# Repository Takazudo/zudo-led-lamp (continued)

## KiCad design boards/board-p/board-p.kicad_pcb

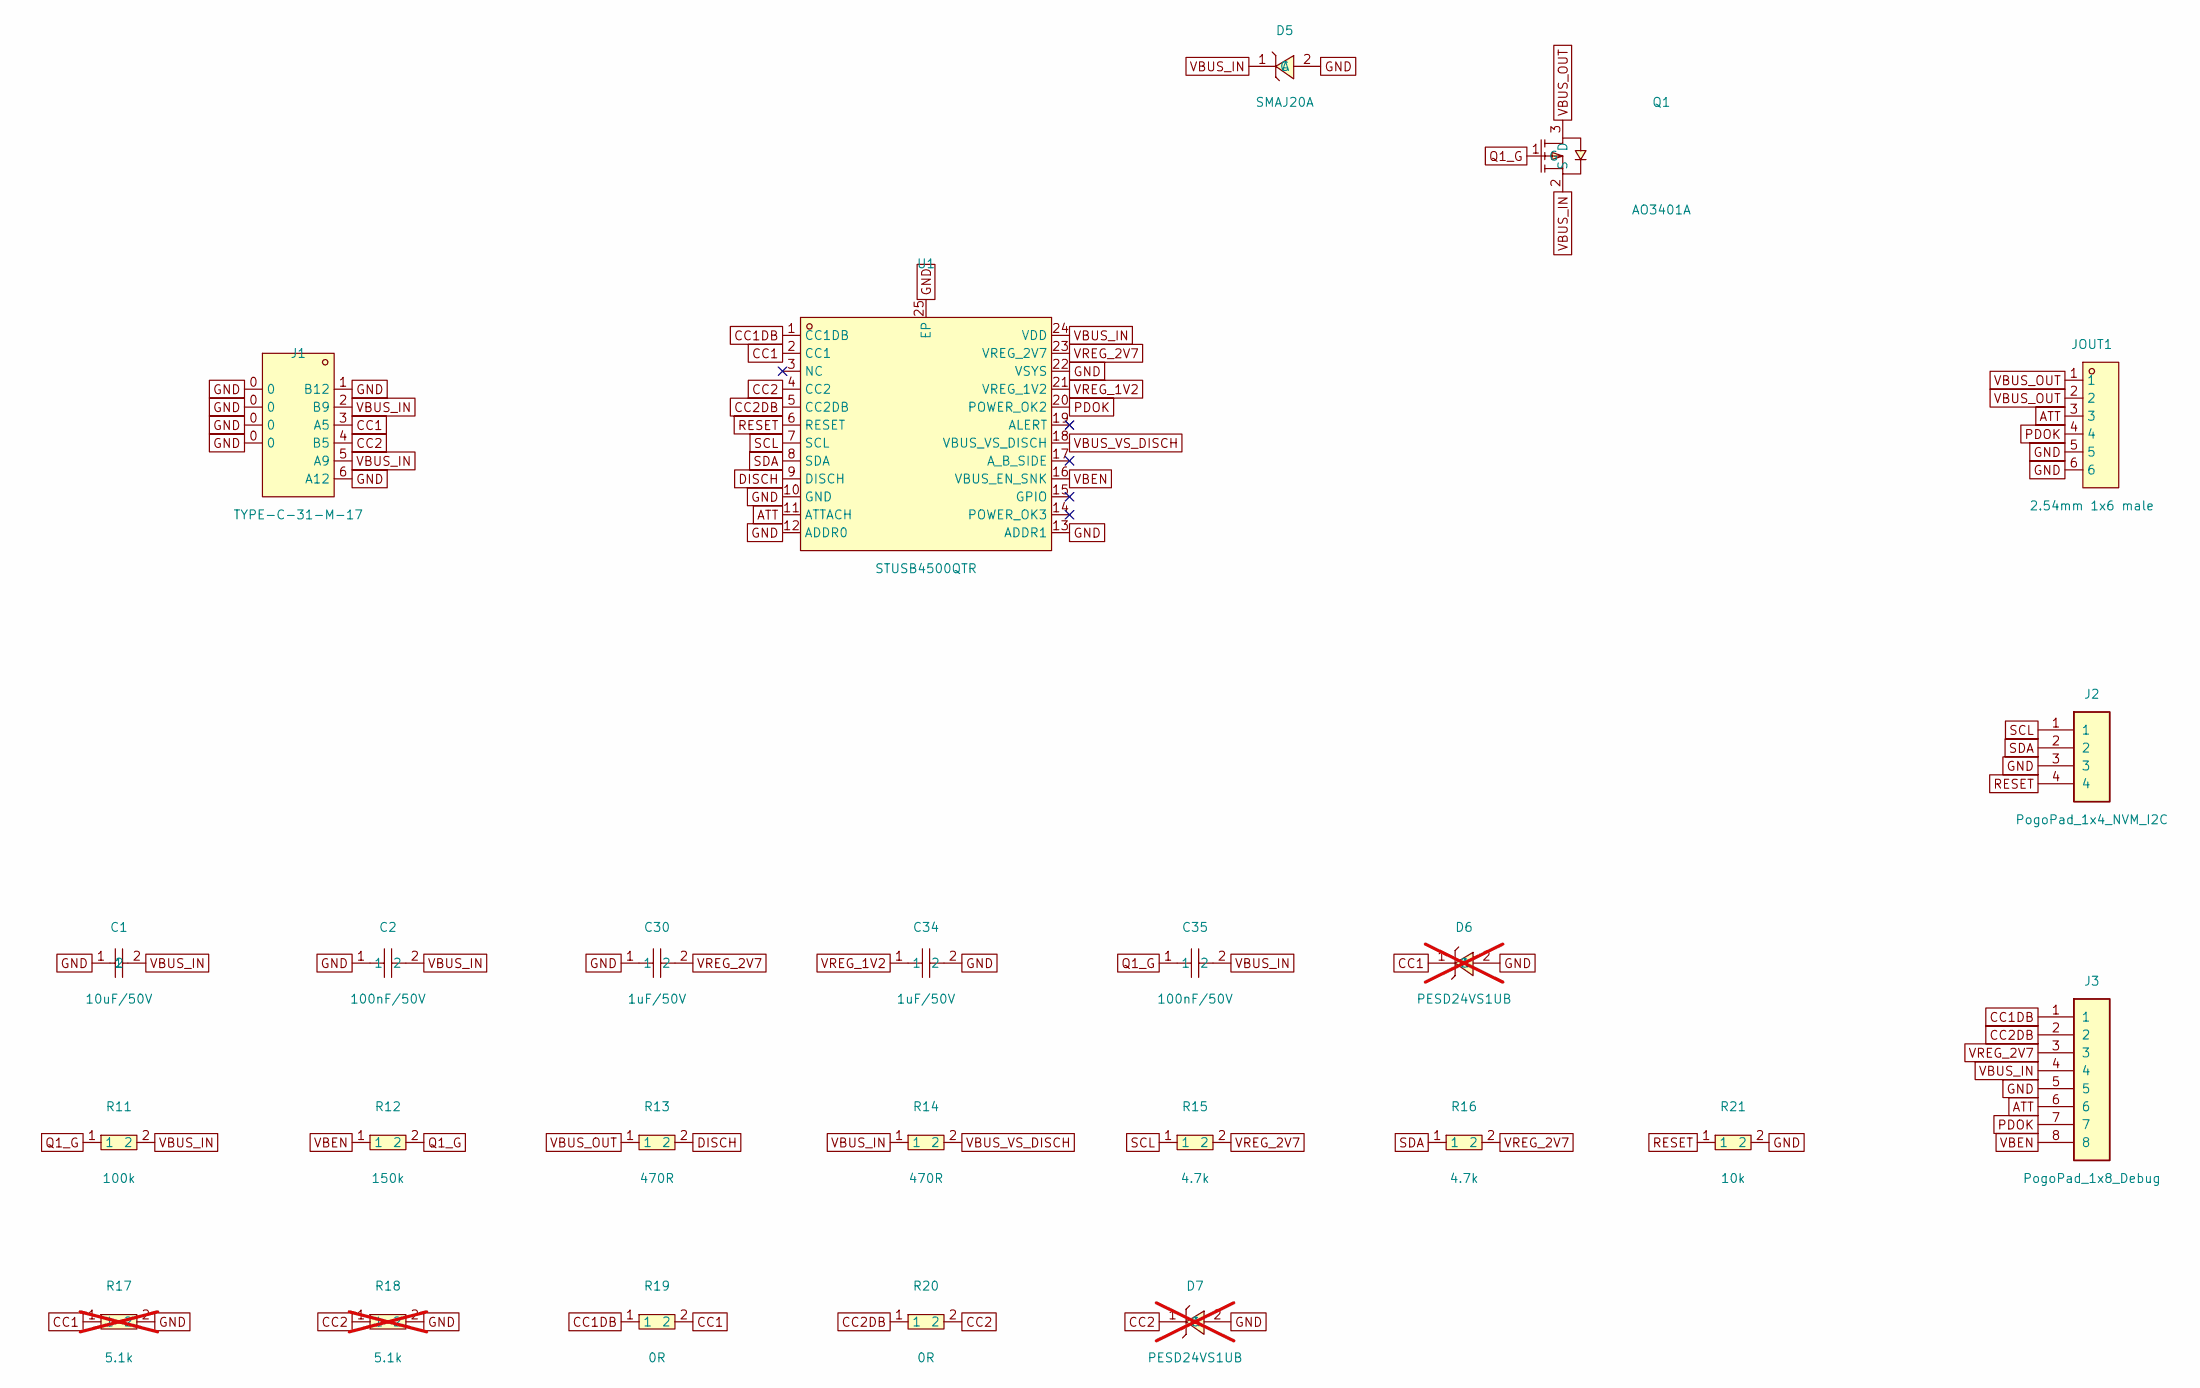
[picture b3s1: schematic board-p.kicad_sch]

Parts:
C1: 10uF/50V; C1206; LCSC C13585
C2, C35: 100nF/50V; C0603; LCSC C14663
C30, C34: 1uF/50V; C0603; LCSC C15849
D5: SMAJ20A; SMA_L4.2-W2.6-LS5.3-RD; LCSC C571370
D6, D7: PESD24VS1UB; SOD-523_L1.2-W0.8-LS1.6-RD; LCSC C85382; not fitted
J1: TYPE-C-31-M-17; USB-C-SMD_10P-P1.00-L6.8-W8.9; LCSC C283540
J2: PogoPad_1x4_NVM_I2C; PogoPad_1x04_P2.54mm
J3: PogoPad_1x8_Debug; PogoPad_1x08_P2.54mm
JOUT1: 2.54mm 1x6 male; HDR-TH_6P-P2.54-V-M; LCSC C492405
Q1: AO3401A; SOT-23_L2.9-W1.3-P1.90-LS2.4-BR; LCSC C347476
R11: 100k; R0603; LCSC C25803
R12: 150k; R0603; LCSC C22807
R13, R14: 470R; R0603; LCSC C23179
R15, R16: 4.7k; R0603; LCSC C23162
R17, R18: 5.1k; R0603; LCSC C23186; not fitted
R19, R20: 0R; R0603; LCSC C21189
R21: 10k; R0805; LCSC C17414
U1: STUSB4500QTR; QFN-24_L4.0-W4.0-P0.50-BL-EP2.8; LCSC C2678061

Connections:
ATT: J3.6, JOUT1.3, U1.11 (ATTACH)
CC1: D6.1 (C), J1.3 (A5), R17.1, R19.2, U1.2 (CC1)
CC1DB: J3.1, R19.1, U1.1 (CC1DB)
CC2: D7.1 (C), J1.4 (B5), R18.1, R20.2, U1.4 (CC2)
CC2DB: J3.2, R20.1, U1.5 (CC2DB)
DISCH: R13.2, U1.9 (DISCH)
GND: C1.1, C2.1, C30.1, C34.2, D5.2 (A), D6.2 (A), D7.2 (A), J1.0, J1.1 (B12), J1.6 (A12), J2.3, J3.5, JOUT1.5, JOUT1.6, R17.2, R18.2, R21.2, U1.10 (GND), U1.12 (ADDR0), U1.13 (ADDR1), U1.22 (VSYS), U1.25 (EP)
PDOK: J3.7, JOUT1.4, U1.20 (POWER_OK2)
Q1_G: C35.1, Q1.1 (G), R11.1, R12.2
RESET: J2.4, R21.1, U1.6 (RESET)
SCL: J2.1, R15.1, U1.7 (SCL)
SDA: J2.2, R16.1, U1.8 (SDA)
VBEN: J3.8, R12.1, U1.16 (VBUS_EN_SNK)
VBUS_IN: C1.2, C2.2, C35.2, D5.1 (C), J1.2 (B9), J1.5 (A9), J3.4, Q1.2 (S), R11.2, R14.1, U1.24 (VDD)
VBUS_OUT: JOUT1.1, JOUT1.2, Q1.3 (D), R13.1
VBUS_VS_DISCH: R14.2, U1.18 (VBUS_VS_DISCH)
VREG_1V2: C34.1, U1.21 (VREG_1V2)
VREG_2V7: C30.2, J3.3, R15.2, R16.2, U1.23 (VREG_2V7)

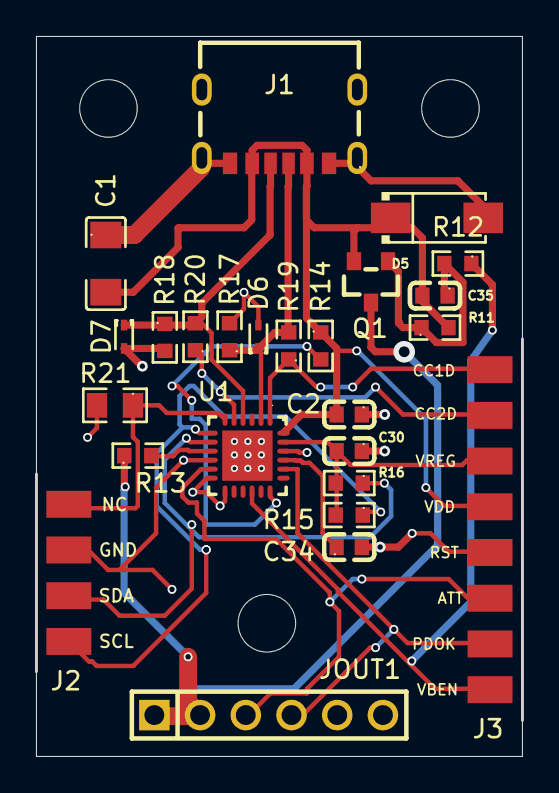
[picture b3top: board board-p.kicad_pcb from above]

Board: 2 copper layers, 27.0 x 40.0 mm, 25 parts (0 on the bottom side), 18 nets.

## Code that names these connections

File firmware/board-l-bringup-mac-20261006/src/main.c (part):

#include <stdint.h>
#include "stm32g0xx.h"

/* Board L bring-up firmware: knob (PA0) -> gamma -> 20 kHz PWM (PA6) into the
 * CTRL RC filter, NTC (PA4) thermal derate, status over USART2 (J4, 115200 8N1).
 * No flame modulation yet. Pin map: doc/src/content/docs/architecture/board-l.mdx. */

#define FRAME_MS            20
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/* CTRL window from the R20/R21 divider and the AL8860 0.3-2.5 V analog range
 * (board-l.mdx "Modulation algorithm"). Raise DUTY_FLOOR_Q16 above the
 * pulse-skip point recorded at Gate 4 if it bursts below ~300 Hz. */
#define DUTY_FLOOR_Q16      10617u   /* CTRL 0.41 V -> 5% of I_NOM */
#define DUTY_FULL_Q16       65535u   /* CTRL 2.53 V -> 100%        */

#define PWM_HZ              20000u
#define PWM_PERIOD          (64000000u / PWM_HZ)   /* 3200 timer ticks */
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    GPIOA->MODER &= ~(3u << (pin * 2));
}

/* PA6 stays in its reset (analog, Hi-Z) state until TIM3 is running at 0% duty,
 * so R21 holds CTRL low throughout init. PA13/PA14 (SWD) and PA15 (bonded to the
 * SWCLK pin) are never touched. */
static void pwm_init(void)
{
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    TIM3->EGR = TIM_EGR_UG;
    TIM3->CR1 |= TIM_CR1_CEN;

    gpio_set_af(6, 1);   /* PA6 = TIM3_CH1 */
}

static void pwm_set_duty_q16(uint32_t duty_q16)
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
static void uart_init(void)
{
    gpio_set_af(2, 1);   /* PA2 = USART2_TX */
    gpio_set_af(3, 1);   /* PA3 = USART2_RX */
    USART2->BRR = (64000000u + 115200u / 2u) / 115200u;
    USART2->CR1 = USART_CR1_TE | USART_CR1_RE | USART_CR1_UE;
}
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    pwm_init();
    uart_init();
    adc_init();
    gpio_set_input(5);   /* PA5 = PDOK, R24 pull-up */
    gpio_set_input(7);   /* PA7 = ATT,  R25 pull-up */

    uart_puts("\r\nzudo-led-lamp bring-up fw\r\n");

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            uart_field("target", target);
            uart_field("level", current);
            uart_field("duty_pct10", duty * 1000u / 65536u);
            uart_field("pdok", (GPIOA->IDR >> 5) & 1u);
            uart_field("att", (GPIOA->IDR >> 7) & 1u);
            uart_puts("\r\n");
        }
    }
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
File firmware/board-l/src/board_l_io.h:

#ifndef BOARD_L_IO_H
#define BOARD_L_IO_H
#include "lamp_control.h"
/* Project connectivity only, NOT a verified STM32 peripheral mapping.
   scripts/schgen/board_l_spec.py NETS, STM32G031F8P6/C529334 U3:
   U3.7 PA0 BRIGHT_ADC; U3.11 PA4 NTC_SENSE; U3.13 PA6 PWM_DIM -> R20 -> CTRL.
   U3.12 PA5 legacy PDOK and U3.14 PA7 legacy ATT have local 10k pullups;
   shared HUSB Board P contacts 4/3 are NC. Never use these as admission inputs.
   U3.18 SWDIO, U3.19 SWCLK, U3.6 NRST. Debug is not power isolation.
*/
enum board_l_result { BOARD_L_OK, BOARD_L_UNCONFIGURED, BOARD_L_IO_ERROR, BOARD_L_PREPARING, BOARD_L_ACQUISITION_UNQUALIFIED };
/* Opaque, deliberately undefined. No production defaults provided.
   Future implementation must validate ADC endpoints/reference/settling/freshness,
   NTC conversion/fault/temperature thresholds, PWM mux/period/polarity,
   CTRL transfer and OFF guarantee, tick/ramp duration and recovery policy.
   NULL/incomplete config: report UNCONFIGURED and maintain physical OFF.
   These declarations do not implement or prove that physical OFF. */
struct board_l_config;
enum board_l_result board_l_initialize_off(const struct board_l_config *cfg);
enum board_l_result board_l_read_samples(struct lamp_samples *out);
/* Must reject uninitialized/unconfigured/out-of-range requests, force OFF on
   failure, and return error. Zero means OFF, not an assumed PWM polarity.
   Call on EVERY control tick including failures; cached output is forbidden. */
enum board_l_result board_l_apply_command(uint32_t command);
/* Must establish OFF even without calibration; implementation still missing. */
void board_l_force_off(void);
#endif
